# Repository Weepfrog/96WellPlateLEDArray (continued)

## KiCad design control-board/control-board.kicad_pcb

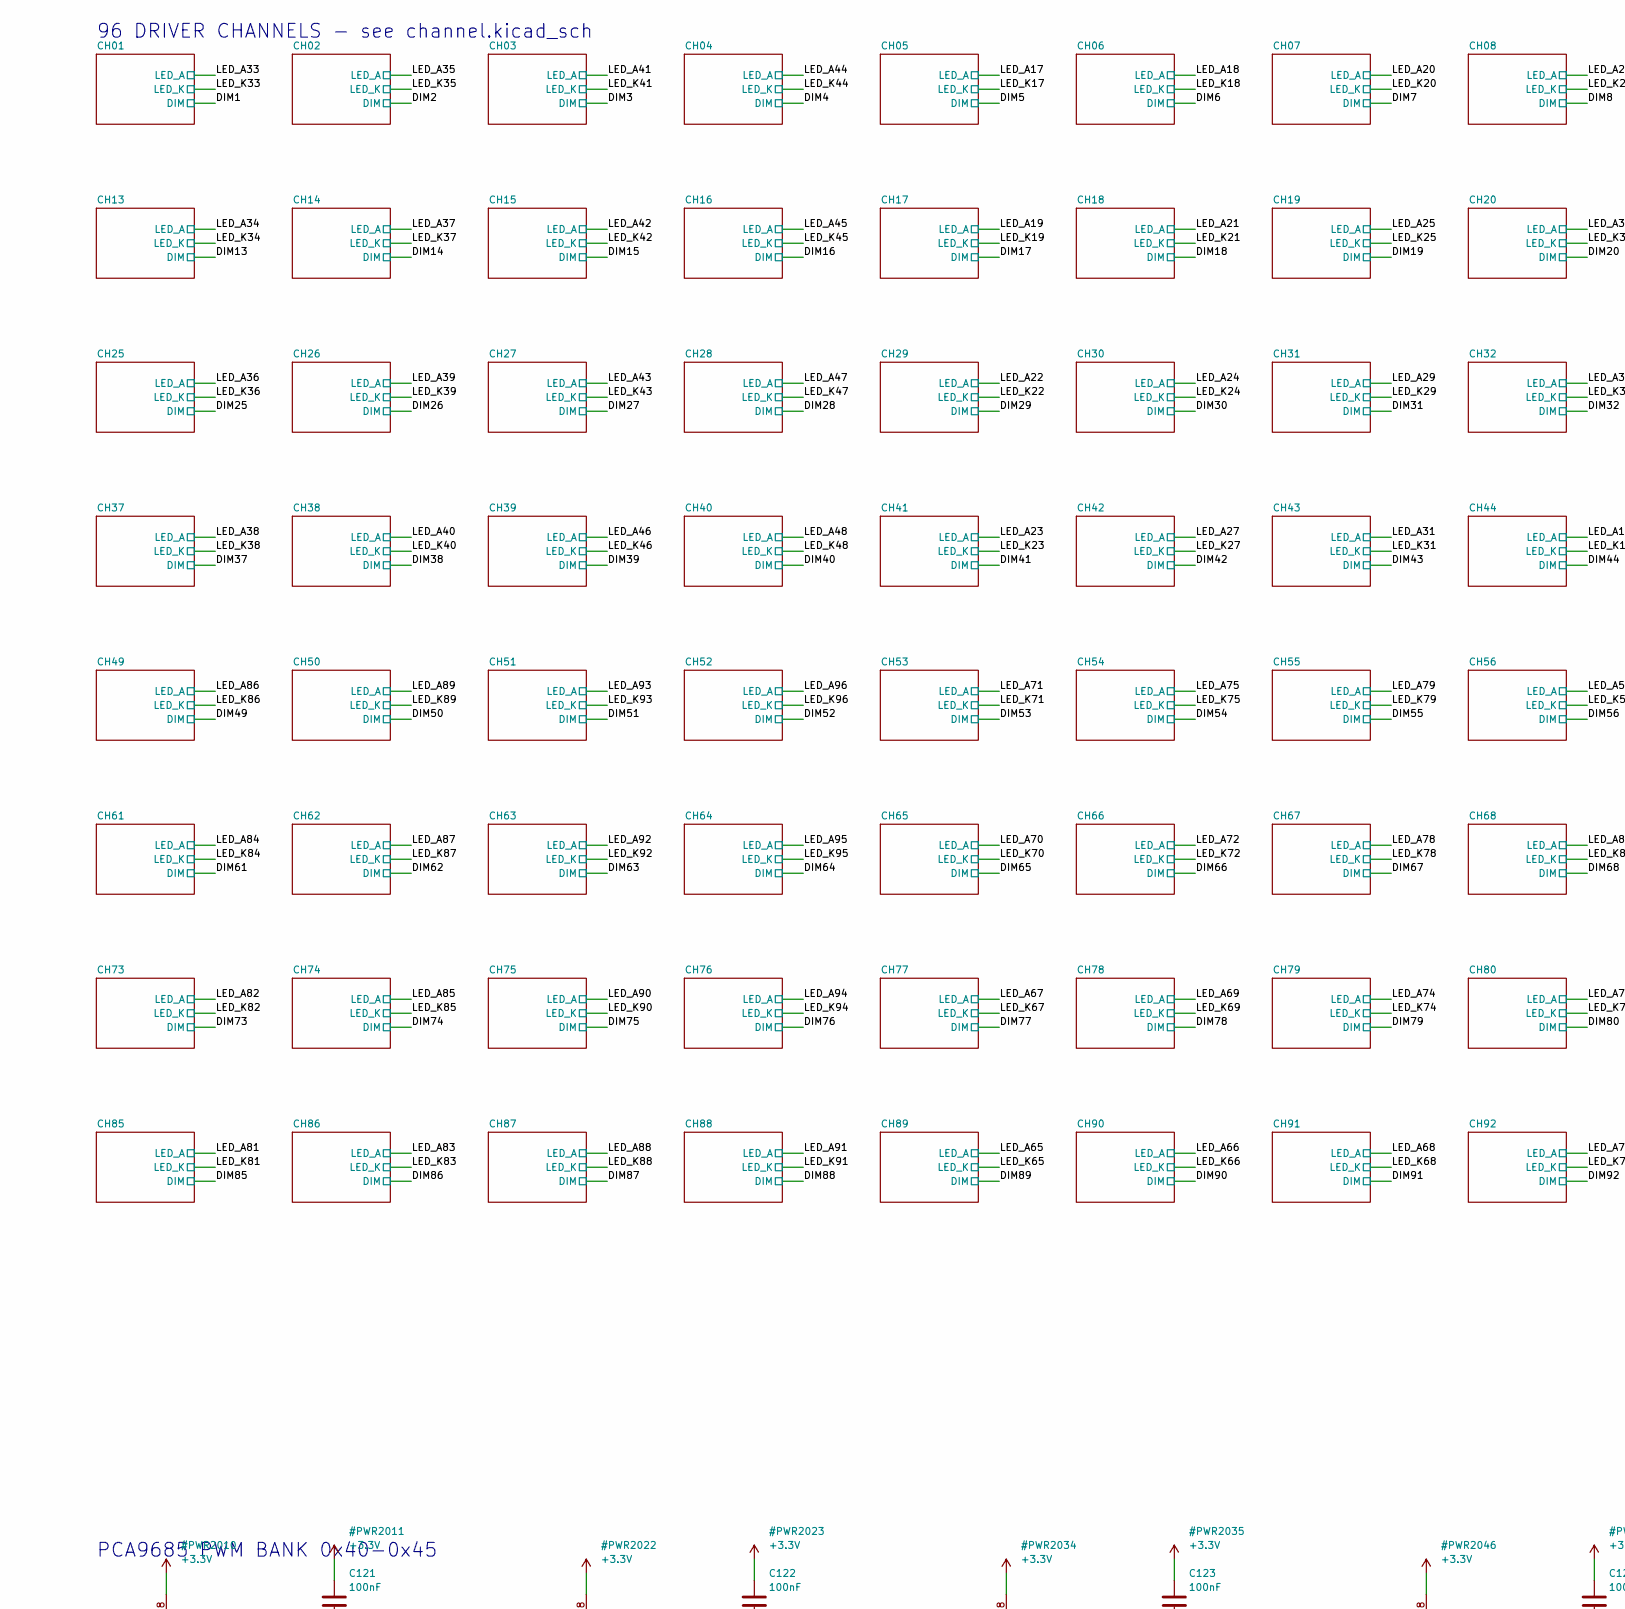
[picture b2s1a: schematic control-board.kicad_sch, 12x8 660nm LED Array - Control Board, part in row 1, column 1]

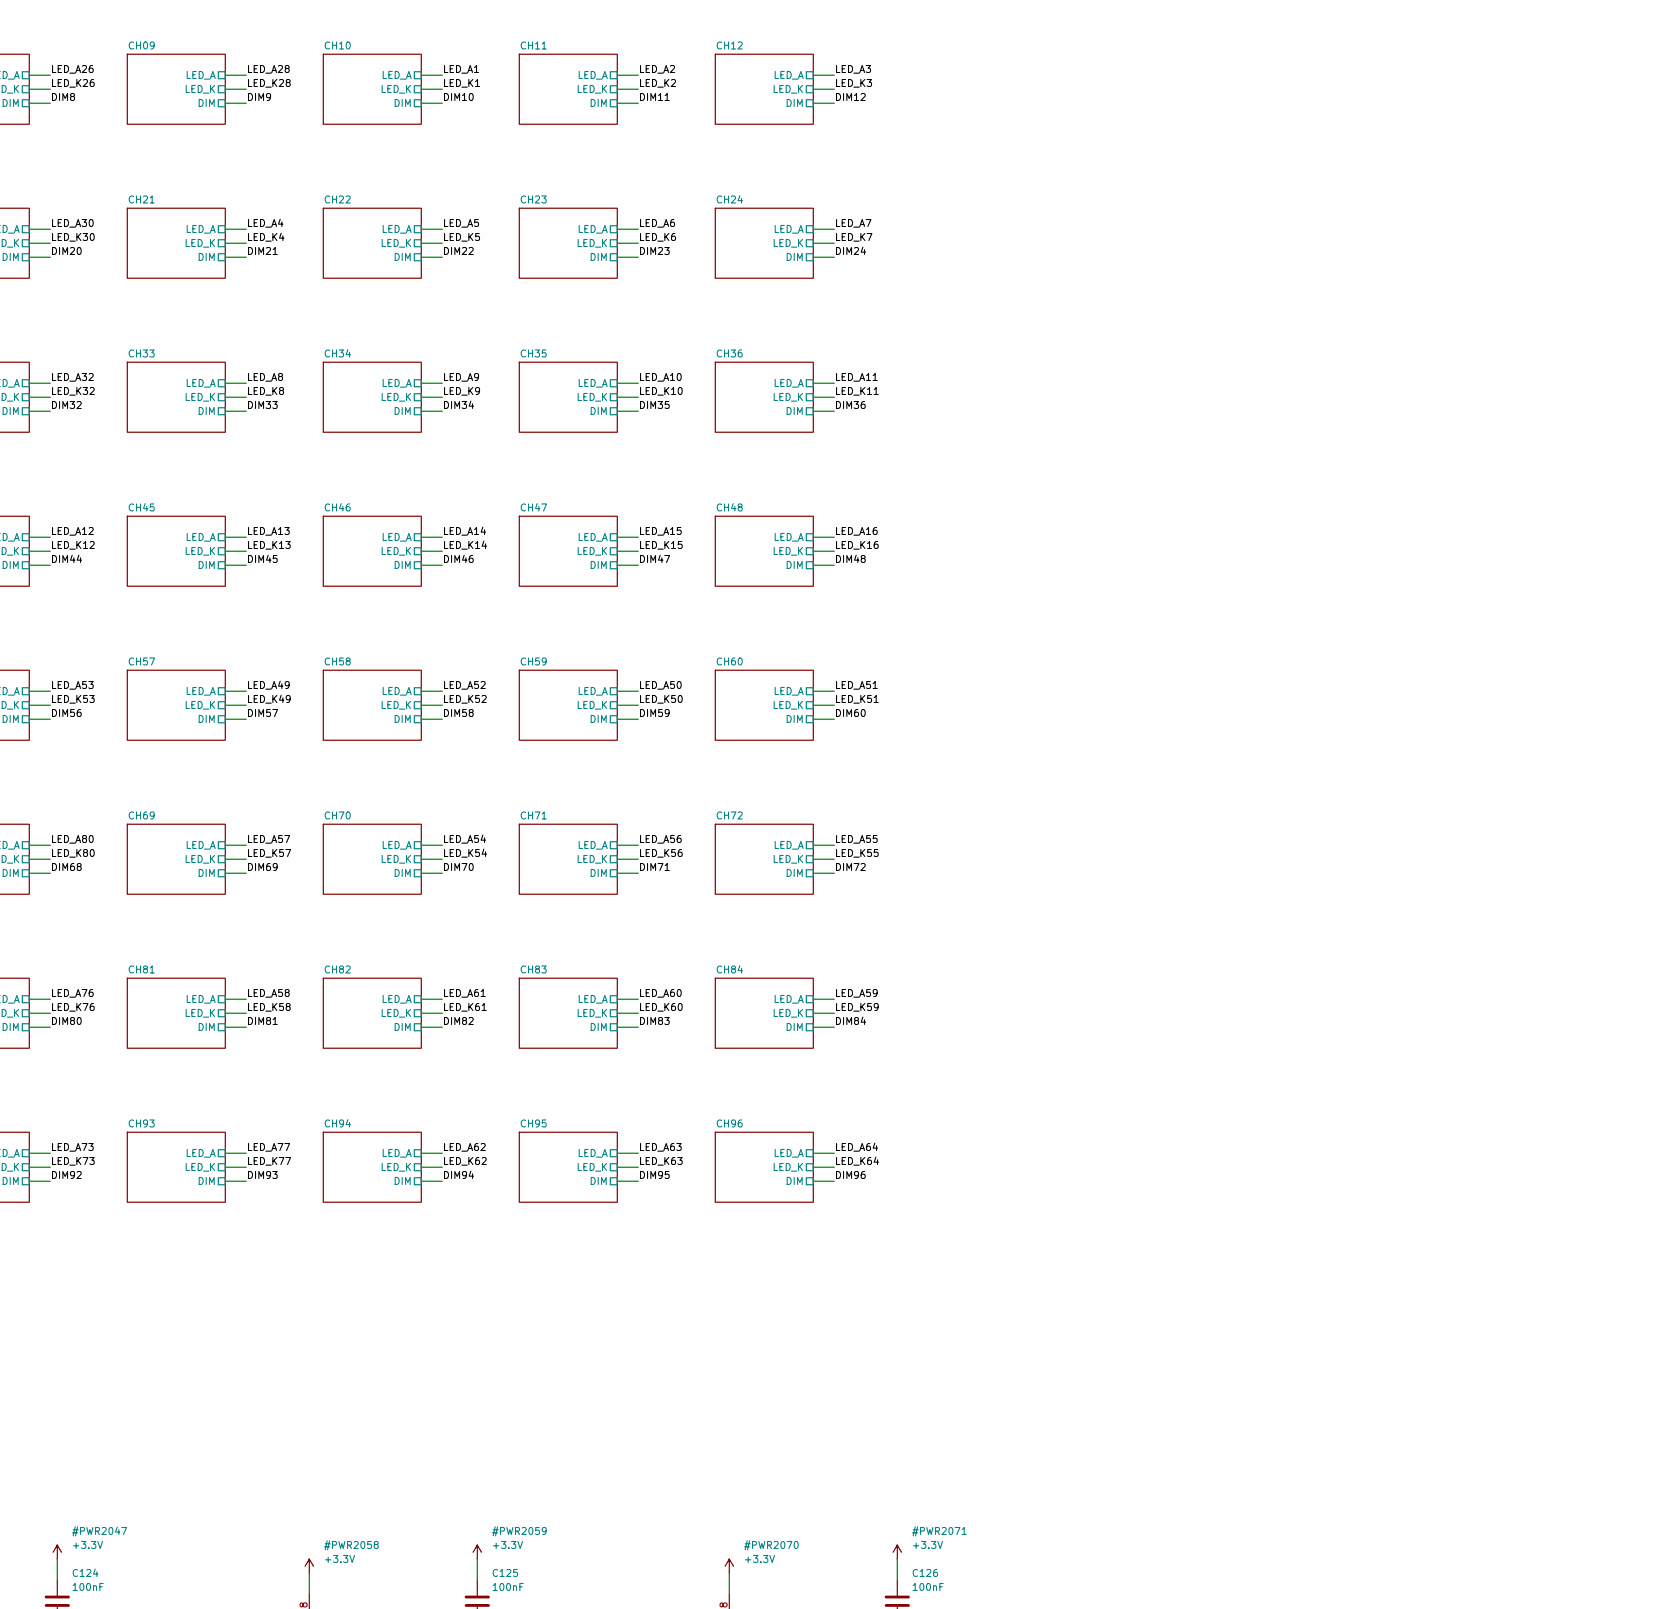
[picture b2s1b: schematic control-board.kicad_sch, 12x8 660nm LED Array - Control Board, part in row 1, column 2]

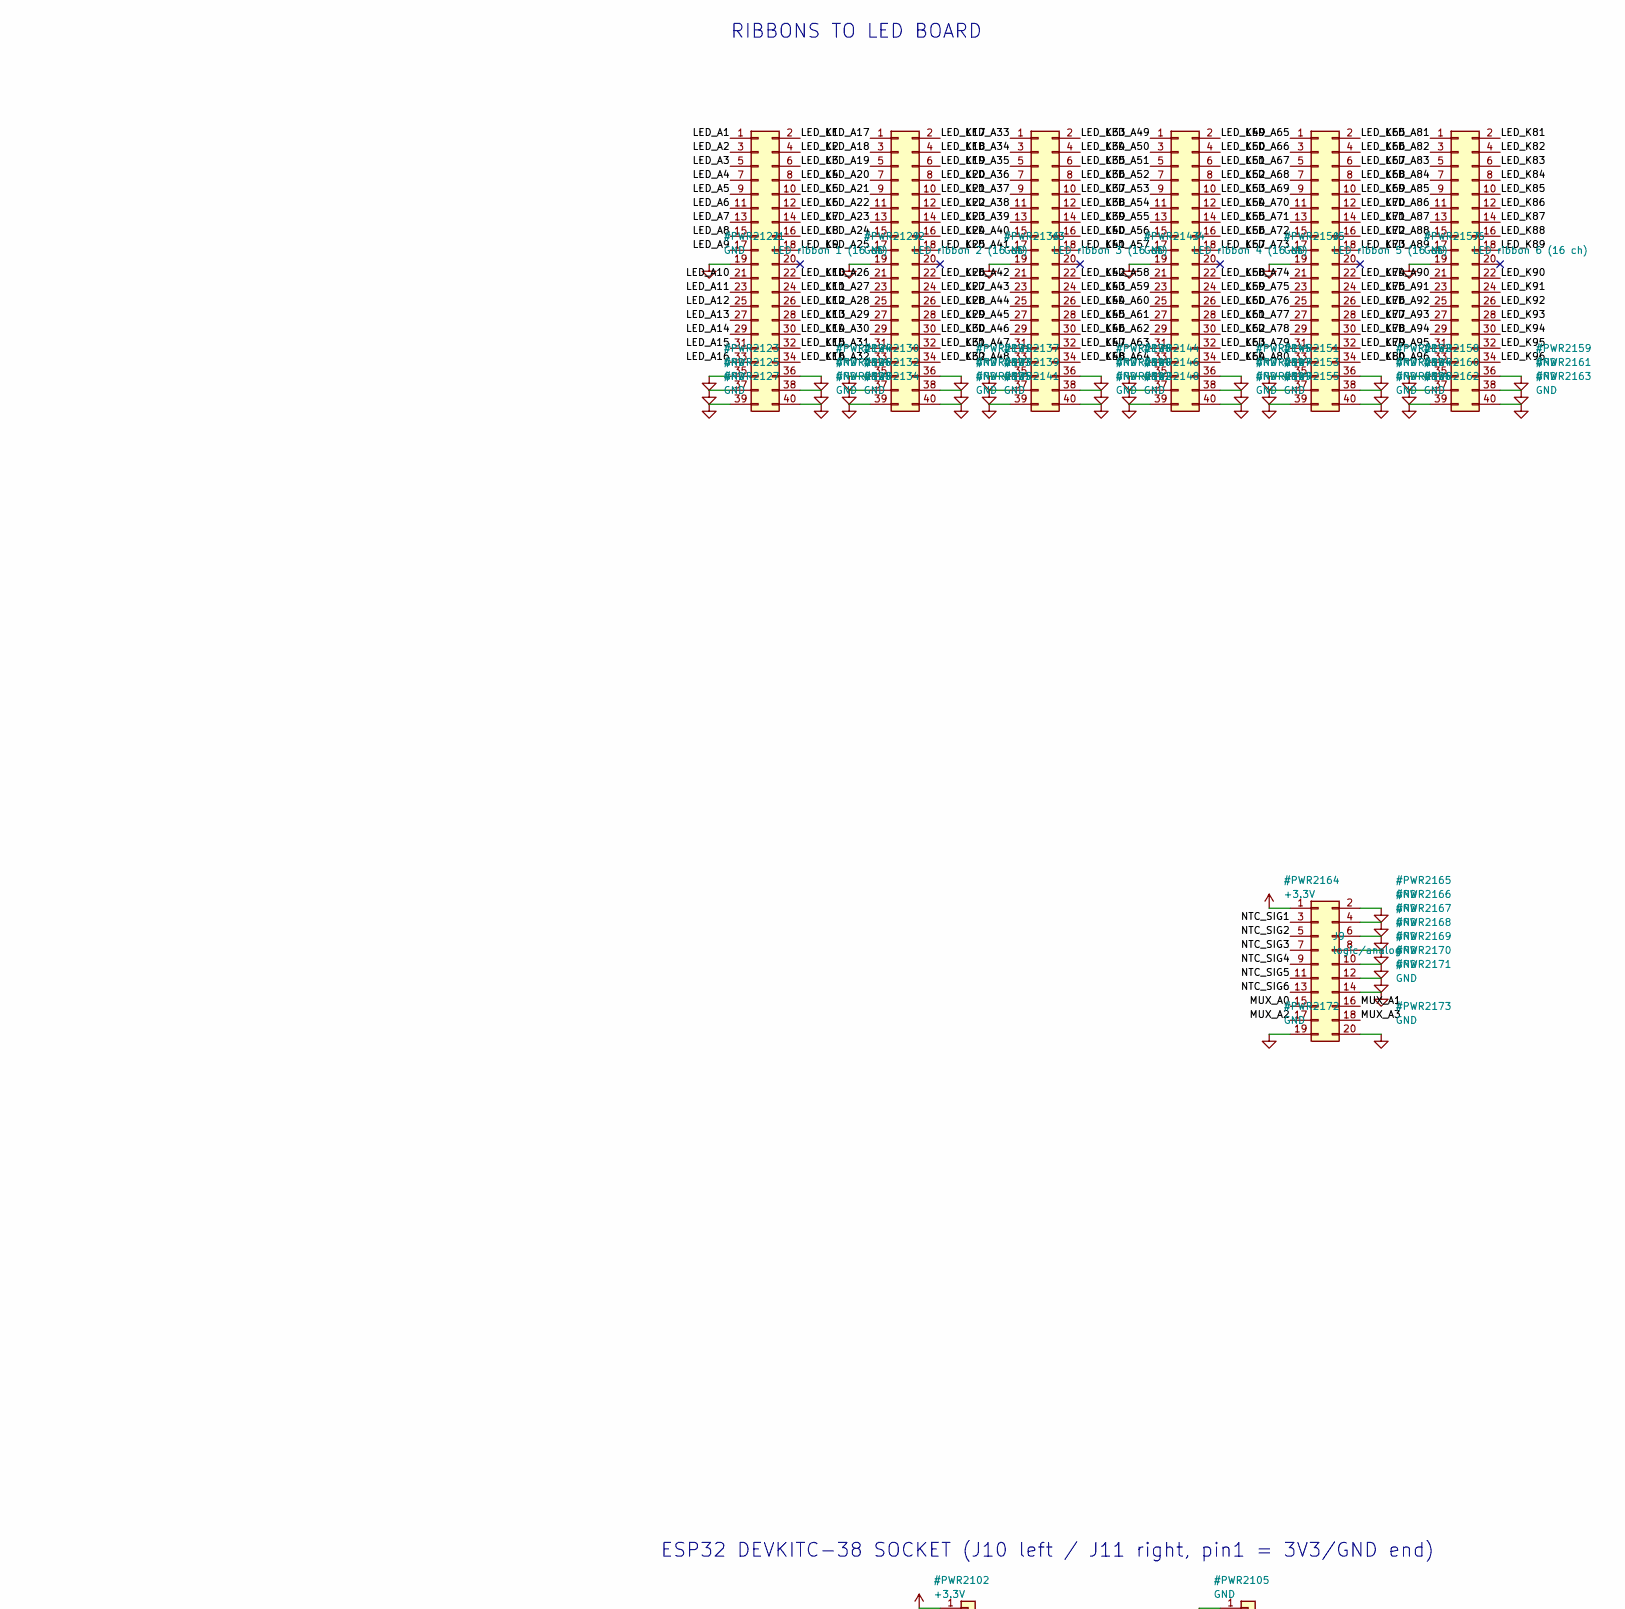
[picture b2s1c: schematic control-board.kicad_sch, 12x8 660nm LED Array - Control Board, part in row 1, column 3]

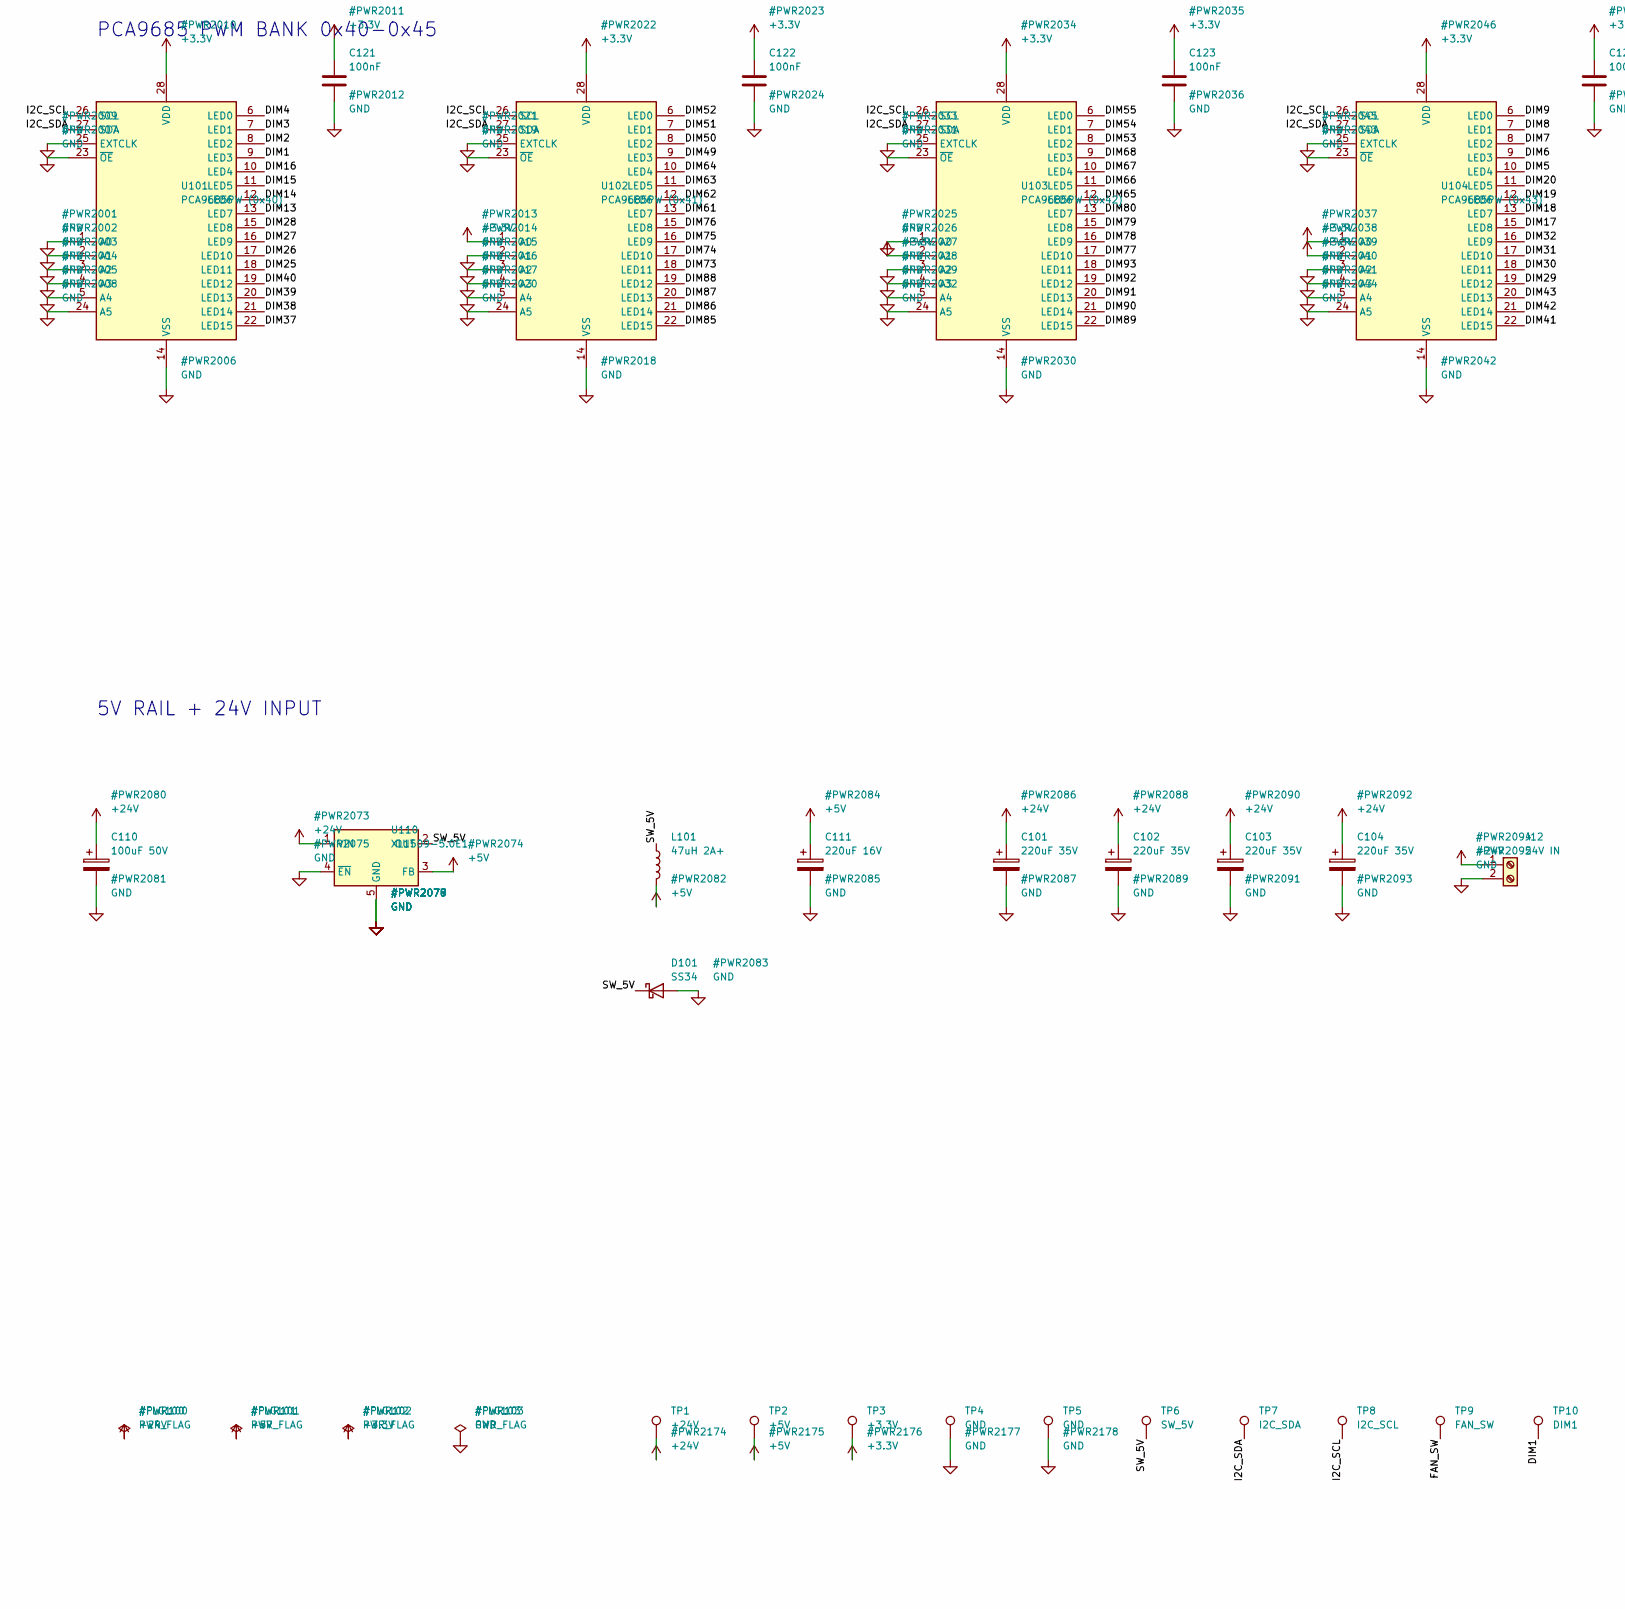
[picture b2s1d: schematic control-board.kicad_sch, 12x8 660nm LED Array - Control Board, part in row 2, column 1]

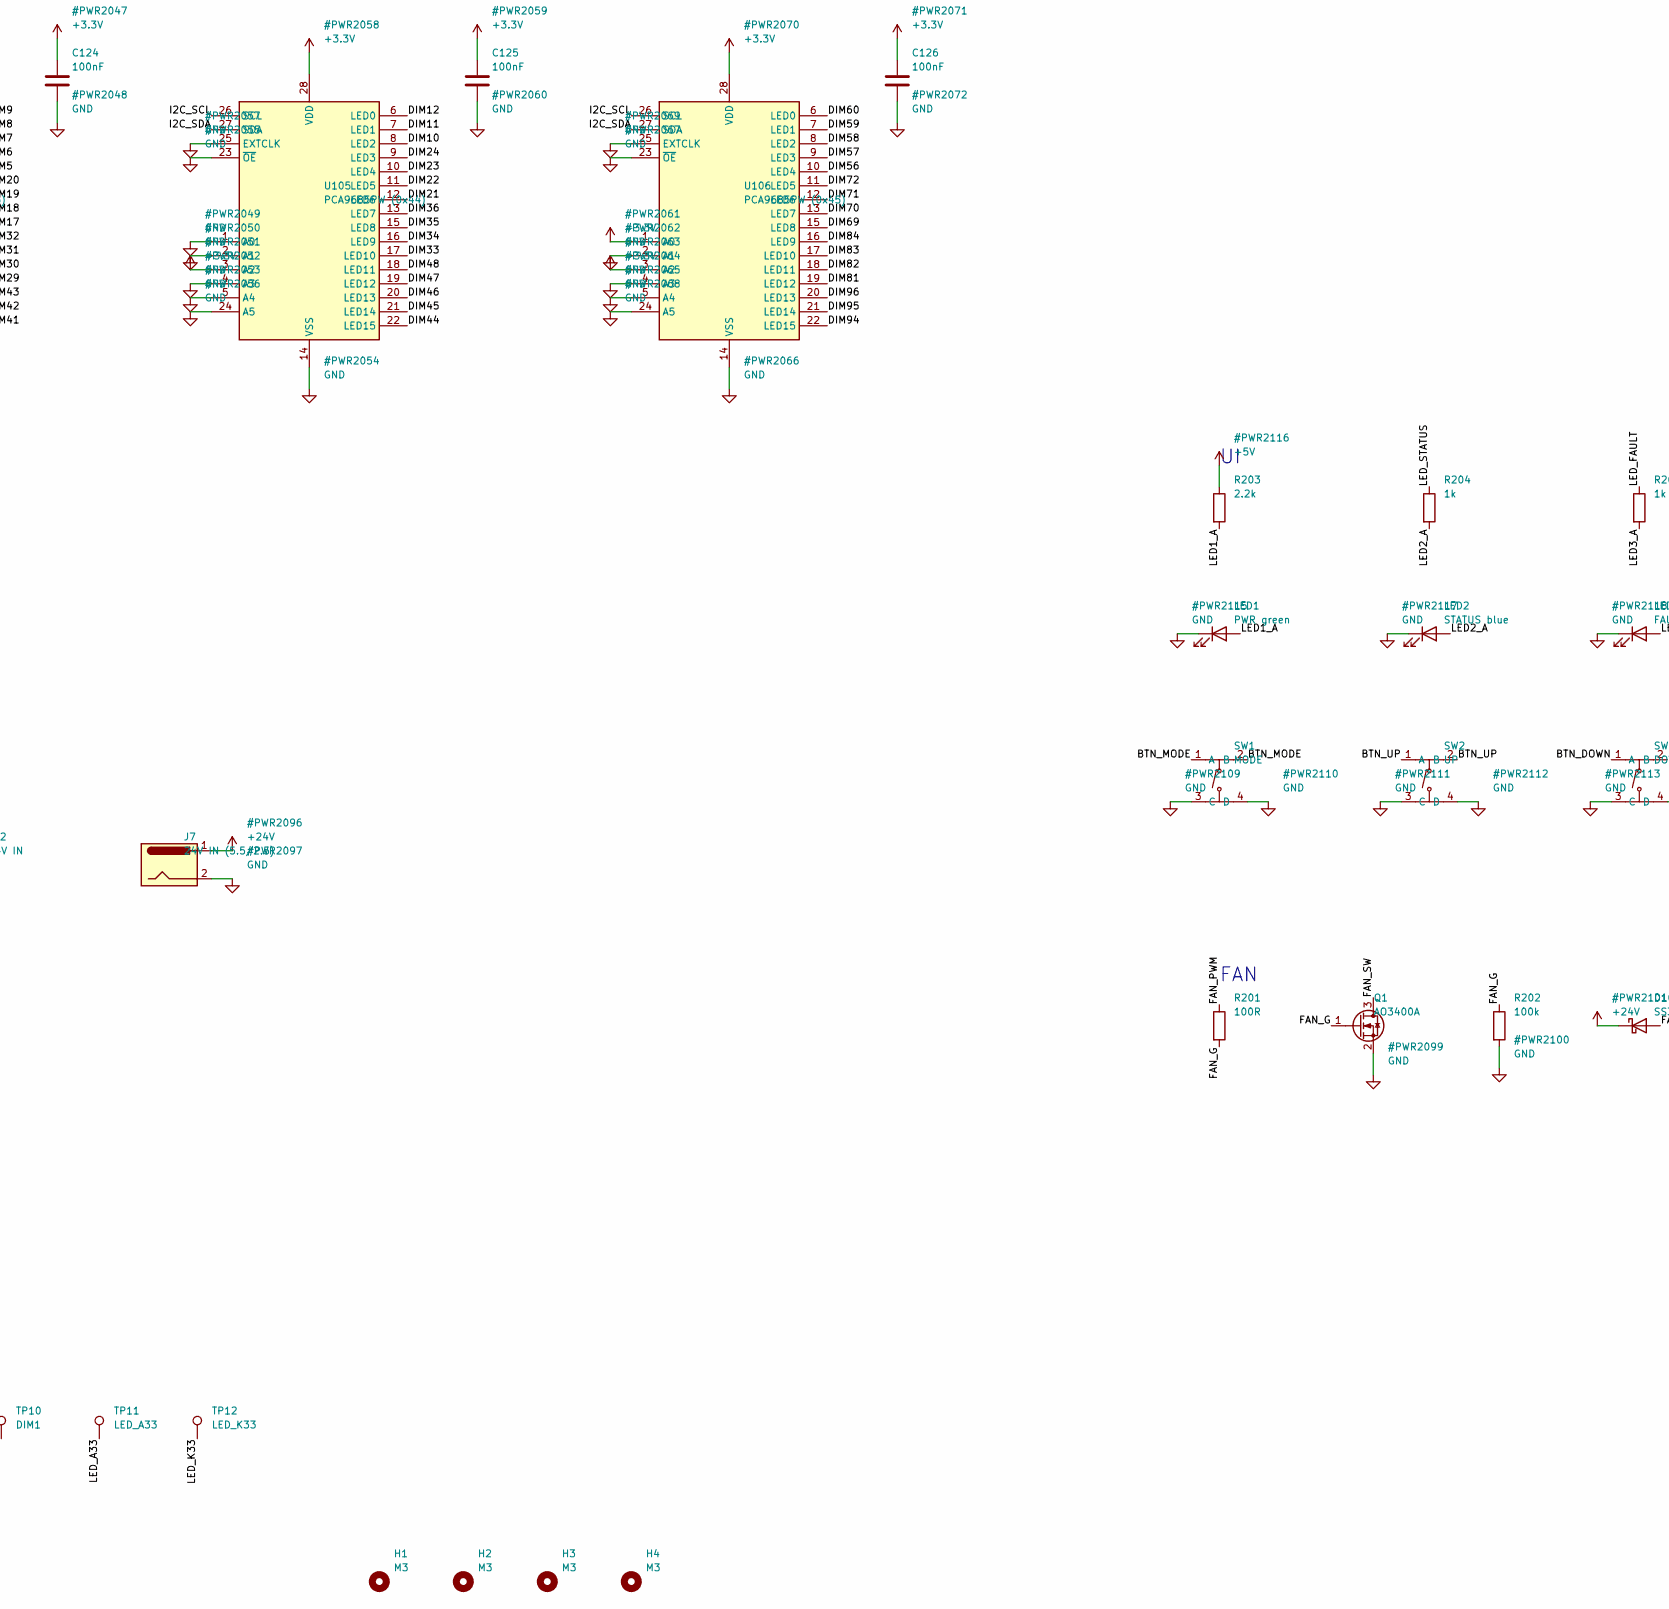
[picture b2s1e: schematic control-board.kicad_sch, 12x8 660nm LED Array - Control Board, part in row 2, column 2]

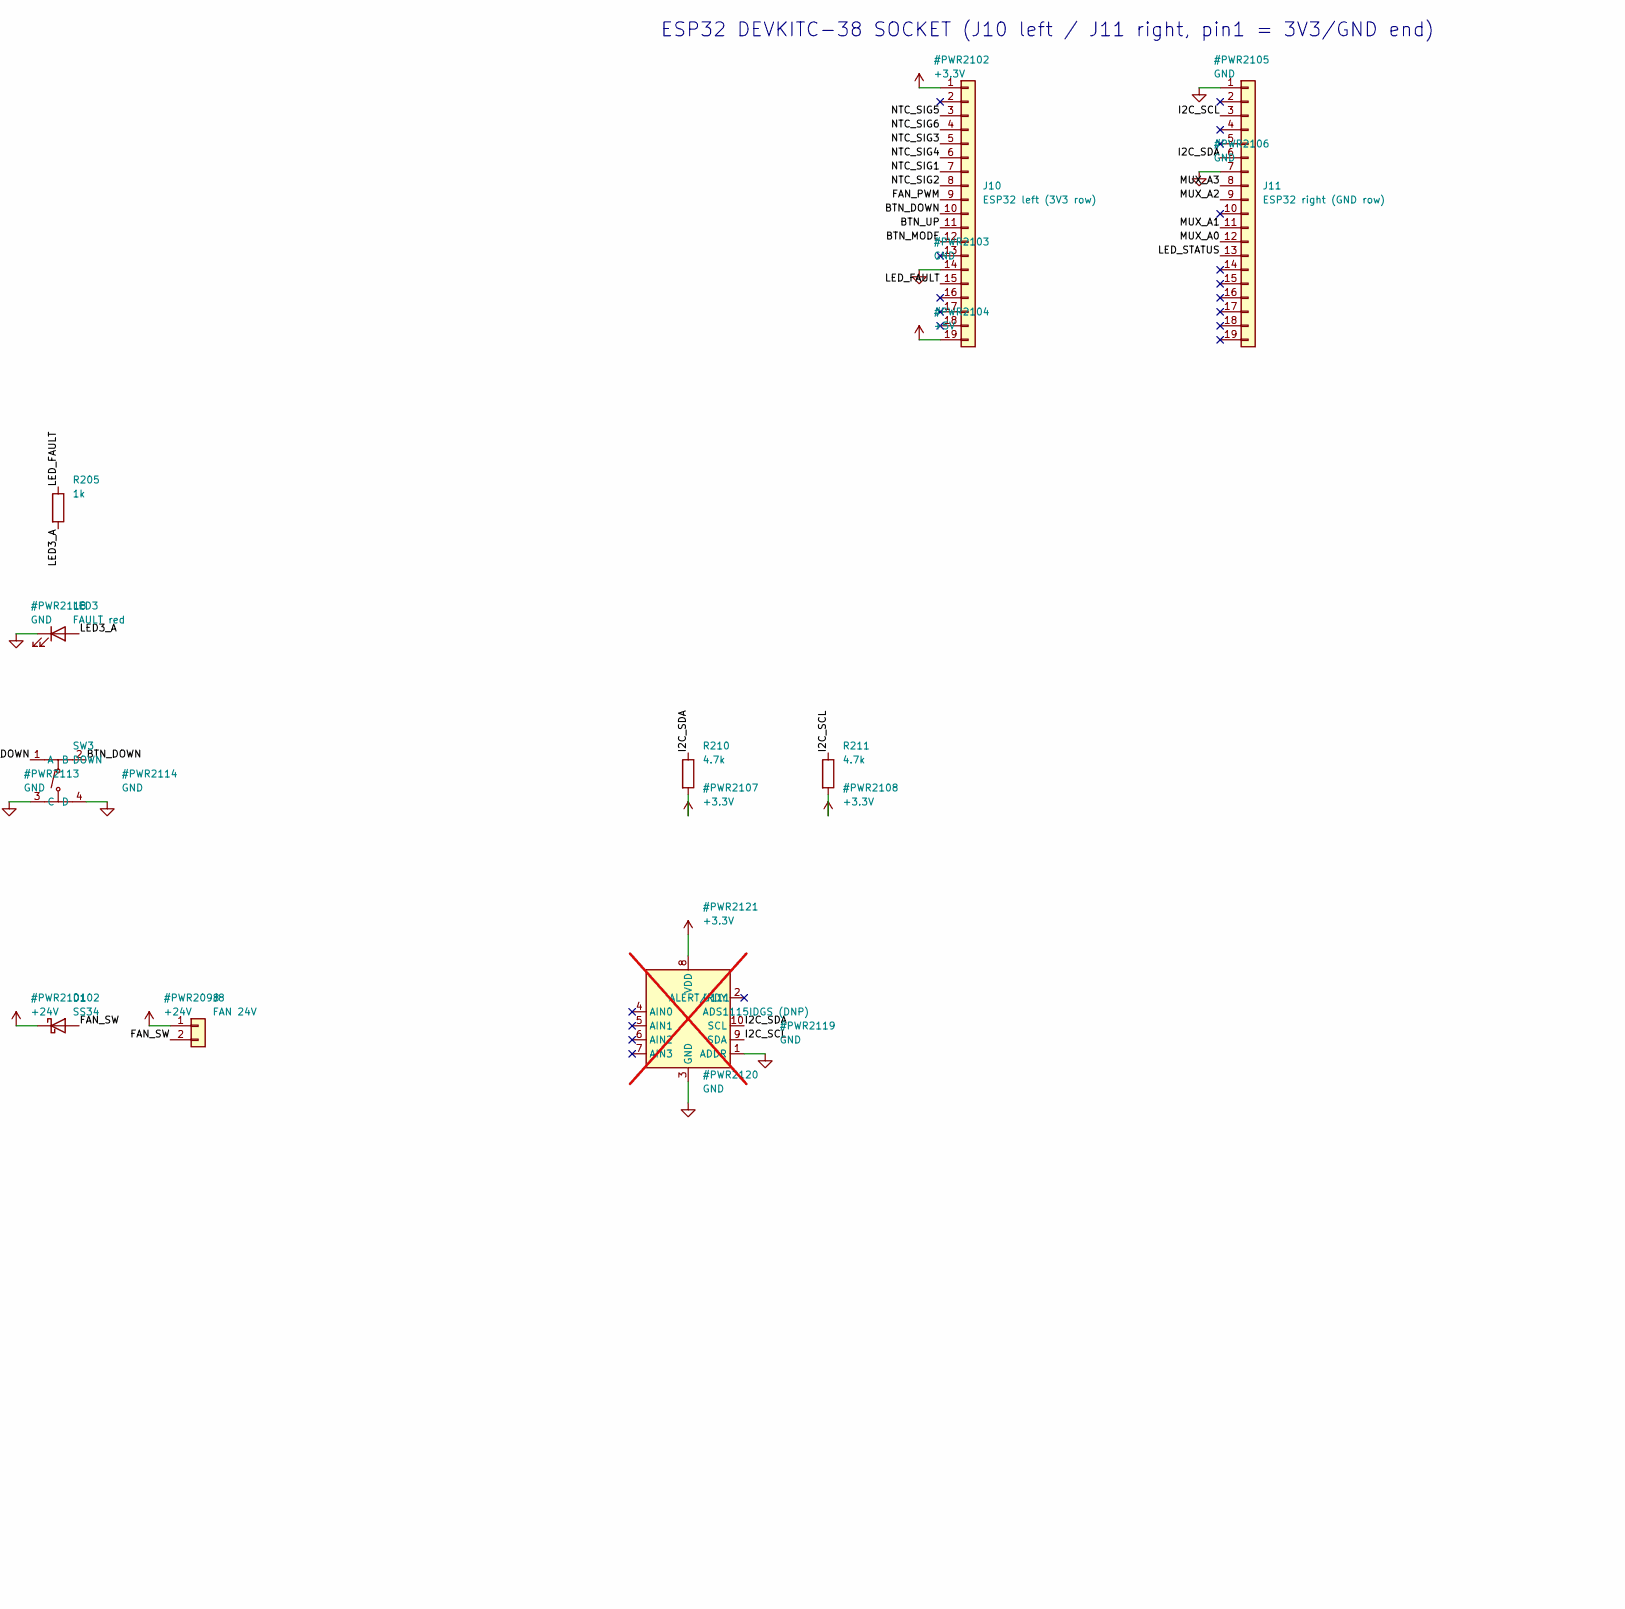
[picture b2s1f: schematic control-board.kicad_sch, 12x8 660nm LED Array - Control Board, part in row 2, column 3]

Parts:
C101, C102, C103, C104: 220uF 35V; CP_Elec_8x10; LCSC C134820
C110: 100uF 50V; CP_Elec_8x10; LCSC C134514
C111: 220uF 16V; CP_Elec_6.3x7.7; LCSC C286136
C121, C122, C123, C124, C125, C126: 100nF; C_0603_1608Metric; LCSC C14663
D101, D102: SS34; D_SMA; LCSC C8678
H1, H2, H3, H4: M3; MountingHole_3.2mm_M3
J1: LED ribbon 1 (16 ch); IDC-Header_2x20_P2.54mm_Vertical; LCSC C9043
J2: LED ribbon 2 (16 ch); IDC-Header_2x20_P2.54mm_Vertical; LCSC C9043
J3: LED ribbon 3 (16 ch); IDC-Header_2x20_P2.54mm_Vertical; LCSC C9043
J4: LED ribbon 4 (16 ch); IDC-Header_2x20_P2.54mm_Vertical; LCSC C9043
J5: LED ribbon 5 (16 ch); IDC-Header_2x20_P2.54mm_Vertical; LCSC C9043
J6: LED ribbon 6 (16 ch); IDC-Header_2x20_P2.54mm_Vertical; LCSC C9043
J7: 24V IN (5.5/2.5); BarrelJack_Horizontal; LCSC C381115
J8: FAN 24V; PinHeader_1x02_P2.54mm_Vertical; LCSC C2337
J9: logic/analog; IDC-Header_2x10_P2.54mm_Horizontal; LCSC C9144
J10: ESP32 left (3V3 row); PinSocket_1x19_P2.54mm_Vertical; LCSC C319202
J11: ESP32 right (GND row); PinSocket_1x19_P2.54mm_Vertical; LCSC C319202
J12: 24V IN; TerminalBlock_KF301-5.0-2P_1x02_P5.00mm; LCSC C474881
L101: 47uH 2A+; L_Sunlord_SWPA6045S; LCSC C36414
LED1: PWR green; LED_0805_2012Metric; LCSC C2297
LED2: STATUS blue; LED_0805_2012Metric; LCSC C2293
LED3: FAULT red; LED_0805_2012Metric; LCSC C84256
Q1: AO3400A; SOT-23; LCSC C20917
R201: 100R; R_0603_1608Metric; LCSC C22775
R202: 100k; R_0603_1608Metric; LCSC C25803
R203: 2.2k; R_0603_1608Metric; LCSC C4190
R204, R205: 1k; R_0603_1608Metric; LCSC C21190
R210, R211: 4.7k; R_0603_1608Metric; LCSC C23162
SW1: MODE; SW-SMD_4P-L5.1-W5.1-P3.70-LS6.5-TL_H1.5; LCSC C318884
SW2: UP; SW-SMD_4P-L5.1-W5.1-P3.70-LS6.5-TL_H1.5; LCSC C318884
SW3: DOWN; SW-SMD_4P-L5.1-W5.1-P3.70-LS6.5-TL_H1.5; LCSC C318884
TP1: +24V; TestPoint_Pad_1.5x1.5mm
TP2: +5V; TestPoint_Pad_1.5x1.5mm
TP3: +3.3V; TestPoint_Pad_1.5x1.5mm
TP4, TP5: GND; TestPoint_Pad_1.5x1.5mm
TP6: SW_5V; TestPoint_Pad_1.5x1.5mm
TP7: I2C_SDA; TestPoint_Pad_1.5x1.5mm
TP8: I2C_SCL; TestPoint_Pad_1.5x1.5mm
TP9: FAN_SW; TestPoint_Pad_1.5x1.5mm
TP10: DIM1; TestPoint_Pad_1.5x1.5mm
TP11: LED_A33; TestPoint_Pad_1.5x1.5mm
TP12: LED_K33; TestPoint_Pad_1.5x1.5mm
U101: PCA9685PW (0x40); TSSOP-28_4.4x9.7mm_P0.65mm; LCSC C2678753
U102: PCA9685PW (0x41); TSSOP-28_4.4x9.7mm_P0.65mm; LCSC C2678753
U103: PCA9685PW (0x42); TSSOP-28_4.4x9.7mm_P0.65mm; LCSC C2678753
U104: PCA9685PW (0x43); TSSOP-28_4.4x9.7mm_P0.65mm; LCSC C2678753
U105: PCA9685PW (0x44); TSSOP-28_4.4x9.7mm_P0.65mm; LCSC C2678753
U106: PCA9685PW (0x45); TSSOP-28_4.4x9.7mm_P0.65mm; LCSC C2678753
U110: XL1509-5.0E1; SOIC-8_3.9x4.9mm_P1.27mm; LCSC C61063
U111: ADS1115IDGS (DNP); TSSOP-10_3x3mm_P0.5mm; LCSC C37593; not fitted

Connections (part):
+3.3V: C121.1, C122.1, C123.1, C124.1, C125.1, C126.1, J9.1, J10.1, R210.2, R211.2, TP3.1 (1_1), U101.28 (VDD), U102.1 (A0), U102.28 (VDD), U103.2 (A1), U103.28 (VDD), U104.1 (A0), U104.2 (A1), U104.28 (VDD), U105.3 (A2), U105.28 (VDD), U106.1 (A0), U106.3 (A2), U106.28 (VDD), U111.8 (VDD)
+5V: C111.1, J10.19, L101.2, R203.1, TP2.1 (1_1), U110.3 (FB)
+24V: C101.1, C102.1, C103.1, C104.1, C110.1, D102.1 (K), J7.1, J8.1, J12.1, TP1.1 (1_1), U110.1 (VIN); also elsewhere on the board
/BTN_DOWN: J10.10, SW3.1 (A), SW3.2 (B)
/BTN_MODE: J10.12, SW1.1 (A), SW1.2 (B)
/BTN_UP: J10.11, SW2.1 (A), SW2.2 (B)
/DIM1: TP10.1 (1_1), U101.9 (LED3); also elsewhere on the board
/DIM2: U101.8 (LED2); also elsewhere on the board
/DIM3: U101.7 (LED1); also elsewhere on the board
/DIM4: U101.6 (LED0); also elsewhere on the board
/DIM5: U104.10 (LED4); also elsewhere on the board
/DIM6: U104.9 (LED3); also elsewhere on the board
/DIM7: U104.8 (LED2); also elsewhere on the board
/DIM8: U104.7 (LED1); also elsewhere on the board
/DIM9: U104.6 (LED0); also elsewhere on the board
/DIM10: U105.8 (LED2); also elsewhere on the board
/DIM11: U105.7 (LED1); also elsewhere on the board
/DIM12: U105.6 (LED0); also elsewhere on the board
/DIM13: U101.13 (LED7); also elsewhere on the board
/DIM14: U101.12 (LED6); also elsewhere on the board
/DIM15: U101.11 (LED5); also elsewhere on the board
/DIM16: U101.10 (LED4); also elsewhere on the board
/DIM17: U104.15 (LED8); also elsewhere on the board
/DIM18: U104.13 (LED7); also elsewhere on the board
/DIM19: U104.12 (LED6); also elsewhere on the board
/DIM20: U104.11 (LED5); also elsewhere on the board
/DIM21: U105.12 (LED6); also elsewhere on the board
/DIM22: U105.11 (LED5); also elsewhere on the board
/DIM23: U105.10 (LED4); also elsewhere on the board
/DIM24: U105.9 (LED3); also elsewhere on the board
/DIM25: U101.18 (LED11); also elsewhere on the board
/DIM26: U101.17 (LED10); also elsewhere on the board
/DIM27: U101.16 (LED9); also elsewhere on the board
/DIM28: U101.15 (LED8); also elsewhere on the board
/DIM29: U104.19 (LED12); also elsewhere on the board
/DIM30: U104.18 (LED11); also elsewhere on the board
/DIM31: U104.17 (LED10); also elsewhere on the board
/DIM32: U104.16 (LED9); also elsewhere on the board
/DIM33: U105.17 (LED10); also elsewhere on the board
/DIM34: U105.16 (LED9); also elsewhere on the board
/DIM35: U105.15 (LED8); also elsewhere on the board
/DIM36: U105.13 (LED7); also elsewhere on the board
/DIM37: U101.22 (LED15); also elsewhere on the board
/DIM38: U101.21 (LED14); also elsewhere on the board
/DIM39: U101.20 (LED13); also elsewhere on the board
/DIM40: U101.19 (LED12); also elsewhere on the board
/DIM41: U104.22 (LED15); also elsewhere on the board
/DIM42: U104.21 (LED14); also elsewhere on the board
/DIM43: U104.20 (LED13); also elsewhere on the board
/DIM44: U105.22 (LED15); also elsewhere on the board
/DIM45: U105.21 (LED14); also elsewhere on the board
/DIM46: U105.20 (LED13); also elsewhere on the board
/DIM47: U105.19 (LED12); also elsewhere on the board
/DIM48: U105.18 (LED11); also elsewhere on the board
/DIM49: U102.9 (LED3); also elsewhere on the board
/DIM50: U102.8 (LED2); also elsewhere on the board
/DIM51: U102.7 (LED1); also elsewhere on the board
/DIM52: U102.6 (LED0); also elsewhere on the board
/DIM53: U103.8 (LED2); also elsewhere on the board
/DIM54: U103.7 (LED1); also elsewhere on the board
/DIM55: U103.6 (LED0); also elsewhere on the board
/DIM56: U106.10 (LED4); also elsewhere on the board
/DIM57: U106.9 (LED3); also elsewhere on the board
/DIM58: U106.8 (LED2); also elsewhere on the board
/DIM59: U106.7 (LED1); also elsewhere on the board
/DIM60: U106.6 (LED0); also elsewhere on the board
/DIM61: U102.13 (LED7); also elsewhere on the board
/DIM62: U102.12 (LED6); also elsewhere on the board
/DIM63: U102.11 (LED5); also elsewhere on the board
/DIM64: U102.10 (LED4); also elsewhere on the board
/DIM65: U103.12 (LED6); also elsewhere on the board
/DIM66: U103.11 (LED5); also elsewhere on the board
/DIM67: U103.10 (LED4); also elsewhere on the board
/DIM68: U103.9 (LED3); also elsewhere on the board
/DIM69: U106.15 (LED8); also elsewhere on the board
/DIM70: U106.13 (LED7); also elsewhere on the board
/DIM71: U106.12 (LED6); also elsewhere on the board
/DIM72: U106.11 (LED5); also elsewhere on the board
/DIM73: U102.18 (LED11); also elsewhere on the board
/DIM74: U102.17 (LED10); also elsewhere on the board
/DIM75: U102.16 (LED9); also elsewhere on the board
/DIM76: U102.15 (LED8); also elsewhere on the board
/DIM77: U103.17 (LED10); also elsewhere on the board
/DIM78: U103.16 (LED9); also elsewhere on the board
/DIM79: U103.15 (LED8); also elsewhere on the board
/DIM80: U103.13 (LED7); also elsewhere on the board
/DIM81: U106.19 (LED12); also elsewhere on the board
/DIM82: U106.18 (LED11); also elsewhere on the board
/DIM83: U106.17 (LED10); also elsewhere on the board
/DIM84: U106.16 (LED9); also elsewhere on the board
/DIM85: U102.22 (LED15); also elsewhere on the board
/DIM86: U102.21 (LED14); also elsewhere on the board
/DIM87: U102.20 (LED13); also elsewhere on the board
/DIM88: U102.19 (LED12); also elsewhere on the board
/DIM89: U103.22 (LED15); also elsewhere on the board
/DIM90: U103.21 (LED14); also elsewhere on the board
/DIM91: U103.20 (LED13); also elsewhere on the board
/DIM92: U103.19 (LED12); also elsewhere on the board
/DIM93: U103.18 (LED11); also elsewhere on the board
/DIM94: U106.22 (LED15); also elsewhere on the board
/DIM95: U106.21 (LED14); also elsewhere on the board
/DIM96: U106.20 (LED13); also elsewhere on the board
/FAN_G: Q1.1 (G), R201.2, R202.1
/FAN_PWM: J10.9, R201.1
/FAN_SW: D102.2 (A), J8.2, Q1.3 (D), TP9.1 (1_1)
/I2C_SCL: J11.3, R211.1, TP8.1 (1_1), U101.26 (SCL), U102.26 (SCL), U103.26 (SCL), U104.26 (SCL), U105.26 (SCL), U106.26 (SCL), U111.9 (SDA)
/I2C_SDA: J11.6, R210.1, TP7.1 (1_1), U101.27 (SDA), U102.27 (SDA), U103.27 (SDA), U104.27 (SDA), U105.27 (SDA), U106.27 (SDA), U111.10 (SCL)
/LED1_A: LED1.2 (A), R203.2
/LED2_A: LED2.2 (A), R204.2
/LED3_A: LED3.2 (A), R205.2
/LED_A1: J1.1; also elsewhere on the board
/LED_A2: J1.3; also elsewhere on the board
/LED_A3: J1.5; also elsewhere on the board
/LED_A4: J1.7; also elsewhere on the board
/LED_A5: J1.9; also elsewhere on the board
/LED_A6: J1.11; also elsewhere on the board
/LED_A7: J1.13; also elsewhere on the board
/LED_A8: J1.15; also elsewhere on the board
/LED_A9: J1.17; also elsewhere on the board
/LED_A10: J1.21; also elsewhere on the board
/LED_A11: J1.23; also elsewhere on the board
/LED_A12: J1.25; also elsewhere on the board
/LED_A13: J1.27; also elsewhere on the board
/LED_A14: J1.29; also elsewhere on the board
/LED_A15: J1.31; also elsewhere on the board
/LED_A16: J1.33; also elsewhere on the board
/LED_A17: J2.1; also elsewhere on the board
/LED_A18: J2.3; also elsewhere on the board
/LED_A19: J2.5; also elsewhere on the board
/LED_A20: J2.7; also elsewhere on the board
/LED_A21: J2.9; also elsewhere on the board
/LED_A22: J2.11; also elsewhere on the board
/LED_A23: J2.13; also elsewhere on the board
/LED_A24: J2.15; also elsewhere on the board
/LED_A25: J2.17; also elsewhere on the board
/LED_A26: J2.21; also elsewhere on the board
/LED_A27: J2.23; also elsewhere on the board
/LED_A28: J2.25; also elsewhere on the board
/LED_A29: J2.27; also elsewhere on the board
/LED_A30: J2.29; also elsewhere on the board
/LED_A31: J2.31; also elsewhere on the board
/LED_A32: J2.33; also elsewhere on the board
/LED_A33: J3.1, TP11.1 (1_1); also elsewhere on the board
/LED_A34: J3.3; also elsewhere on the board
/LED_A35: J3.5; also elsewhere on the board
/LED_A36: J3.7; also elsewhere on the board
/LED_A37: J3.9; also elsewhere on the board
/LED_A38: J3.11; also elsewhere on the board
/LED_A39: J3.13; also elsewhere on the board
/LED_A40: J3.15; also elsewhere on the board
/LED_A41: J3.17; also elsewhere on the board
/LED_A42: J3.21; also elsewhere on the board
/LED_A43: J3.23; also elsewhere on the board
/LED_A44: J3.25; also elsewhere on the board
/LED_A45: J3.27; also elsewhere on the board
/LED_A46: J3.29; also elsewhere on the board
/LED_A47: J3.31; also elsewhere on the board
/LED_A48: J3.33; also elsewhere on the board
/LED_A49: J4.1; also elsewhere on the board
/LED_A50: J4.3; also elsewhere on the board
/LED_A51: J4.5; also elsewhere on the board
/LED_A52: J4.7; also elsewhere on the board
/LED_A53: J4.9; also elsewhere on the board
/LED_A54: J4.11; also elsewhere on the board
/LED_A55: J4.13; also elsewhere on the board
/LED_A56: J4.15; also elsewhere on the board
/LED_A57: J4.17; also elsewhere on the board
/LED_A58: J4.21; also elsewhere on the board
/LED_A59: J4.23; also elsewhere on the board
/LED_A60: J4.25; also elsewhere on the board
/LED_A61: J4.27; also elsewhere on the board
/LED_A62: J4.29; also elsewhere on the board
/LED_A63: J4.31; also elsewhere on the board
/LED_A64: J4.33; also elsewhere on the board
/LED_A65: J5.1; also elsewhere on the board
/LED_A66: J5.3; also elsewhere on the board
/LED_A67: J5.5; also elsewhere on the board
/LED_A68: J5.7; also elsewhere on the board
/LED_A69: J5.9; also elsewhere on the board
/LED_A70: J5.11; also elsewhere on the board
/LED_A71: J5.13; also elsewhere on the board
/LED_A72: J5.15; also elsewhere on the board
/LED_A73: J5.17; also elsewhere on the board
/LED_A74: J5.21; also elsewhere on the board
/LED_A75: J5.23; also elsewhere on the board
/LED_A76: J5.25; also elsewhere on the board
/LED_A77: J5.27; also elsewhere on the board
/LED_A78: J5.29; also elsewhere on the board
/LED_A79: J5.31; also elsewhere on the board
/LED_A80: J5.33; also elsewhere on the board
/LED_A81: J6.1; also elsewhere on the board
/LED_A82: J6.3; also elsewhere on the board
/LED_A83: J6.5; also elsewhere on the board
/LED_A84: J6.7; also elsewhere on the board
/LED_A85: J6.9; also elsewhere on the board
/LED_A86: J6.11; also elsewhere on the board
/LED_A87: J6.13; also elsewhere on the board
/LED_A88: J6.15; also elsewhere on the board
/LED_A89: J6.17; also elsewhere on the board
/LED_A90: J6.21; also elsewhere on the board
/LED_A91: J6.23; also elsewhere on the board
/LED_A92: J6.25; also elsewhere on the board
/LED_A93: J6.27; also elsewhere on the board
/LED_A94: J6.29; also elsewhere on the board
/LED_A95: J6.31; also elsewhere on the board
/LED_A96: J6.33; also elsewhere on the board
/LED_FAULT: J10.15, R205.1
/LED_K1: J1.2; also elsewhere on the board
/LED_K2: J1.4; also elsewhere on the board
/LED_K3: J1.6; also elsewhere on the board
/LED_K4: J1.8; also elsewhere on the board
/LED_K5: J1.10; also elsewhere on the board
/LED_K6: J1.12; also elsewhere on the board
/LED_K7: J1.14; also elsewhere on the board
/LED_K8: J1.16; also elsewhere on the board
/LED_K9: J1.18; also elsewhere on the board
/LED_K10: J1.22; also elsewhere on the board
/LED_K11: J1.24; also elsewhere on the board
/LED_K12: J1.26; also elsewhere on the board
/LED_K13: J1.28; also elsewhere on the board
/LED_K14: J1.30; also elsewhere on the board
/LED_K15: J1.32; also elsewhere on the board
/LED_K16: J1.34; also elsewhere on the board
/LED_K17: J2.2; also elsewhere on the board
/LED_K18: J2.4; also elsewhere on the board
/LED_K19: J2.6; also elsewhere on the board
/LED_K20: J2.8; also elsewhere on the board
/LED_K21: J2.10; also elsewhere on the board
/LED_K22: J2.12; also elsewhere on the board
/LED_K23: J2.14; also elsewhere on the board
/LED_K24: J2.16; also elsewhere on the board
/LED_K25: J2.18; also elsewhere on the board
/LED_K26: J2.22; also elsewhere on the board
/LED_K27: J2.24; also elsewhere on the board
/LED_K28: J2.26; also elsewhere on the board
/LED_K29: J2.28; also elsewhere on the board
/LED_K30: J2.30; also elsewhere on the board
/LED_K31: J2.32; also elsewhere on the board
/LED_K32: J2.34; also elsewhere on the board
/LED_K33: J3.2, TP12.1 (1_1); also elsewhere on the board
/LED_K34: J3.4; also elsewhere on the board
/LED_K35: J3.6; also elsewhere on the board
/LED_K36: J3.8; also elsewhere on the board
/LED_K37: J3.10; also elsewhere on the board
/LED_K38: J3.12; also elsewhere on the board
/LED_K39: J3.14; also elsewhere on the board
/LED_K40: J3.16; also elsewhere on the board
/LED_K41: J3.18; also elsewhere on the board
/LED_K42: J3.22; also elsewhere on the board
/LED_K43: J3.24; also elsewhere on the board
/LED_K44: J3.26; also elsewhere on the board
/LED_K45: J3.28; also elsewhere on the board
/LED_K46: J3.30; also elsewhere on the board
/LED_K47: J3.32; also elsewhere on the board
/LED_K48: J3.34; also elsewhere on the board
/LED_K49: J4.2; also elsewhere on the board
/LED_K50: J4.4; also elsewhere on the board
/LED_K51: J4.6; also elsewhere on the board
/LED_K52: J4.8; also elsewhere on the board
/LED_K53: J4.10; also elsewhere on the board
/LED_K54: J4.12; also elsewhere on the board
/LED_K55: J4.14; also elsewhere on the board
/LED_K56: J4.16; also elsewhere on the board
/LED_K57: J4.18; also elsewhere on the board
/LED_K58: J4.22; also elsewhere on the board
/LED_K59: J4.24; also elsewhere on the board
/LED_K60: J4.26; also elsewhere on the board
/LED_K61: J4.28; also elsewhere on the board
/LED_K62: J4.30; also elsewhere on the board
/LED_K63: J4.32; also elsewhere on the board
/LED_K64: J4.34; also elsewhere on the board
/LED_K65: J5.2; also elsewhere on the board
/LED_K66: J5.4; also elsewhere on the board
/LED_K67: J5.6; also elsewhere on the board
/LED_K68: J5.8; also elsewhere on the board
/LED_K69: J5.10; also elsewhere on the board
/LED_K70: J5.12; also elsewhere on the board
/LED_K71: J5.14; also elsewhere on the board
/LED_K72: J5.16; also elsewhere on the board
/LED_K73: J5.18; also elsewhere on the board
/LED_K74: J5.22; also elsewhere on the board
/LED_K75: J5.24; also elsewhere on the board
/LED_K76: J5.26; also elsewhere on the board
/LED_K77: J5.28; also elsewhere on the board
/LED_K78: J5.30; also elsewhere on the board
/LED_K79: J5.32; also elsewhere on the board
/LED_K80: J5.34; also elsewhere on the board
/LED_K81: J6.2; also elsewhere on the board
/LED_K82: J6.4; also elsewhere on the board
/LED_K83: J6.6; also elsewhere on the board
/LED_K84: J6.8; also elsewhere on the board
/LED_K85: J6.10; also elsewhere on the board
/LED_K86: J6.12; also elsewhere on the board
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
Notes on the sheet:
96 DRIVER CHANNELS - see channel.kicad_sch
PCA9685 PWM BANK 0x40-0x45
5V RAIL + 24V INPUT
FAN
ESP32 DEVKITC-38 SOCKET (J10 left / J11 right, pin1 = 3V3/GND end)
RIBBONS TO LED BOARD
